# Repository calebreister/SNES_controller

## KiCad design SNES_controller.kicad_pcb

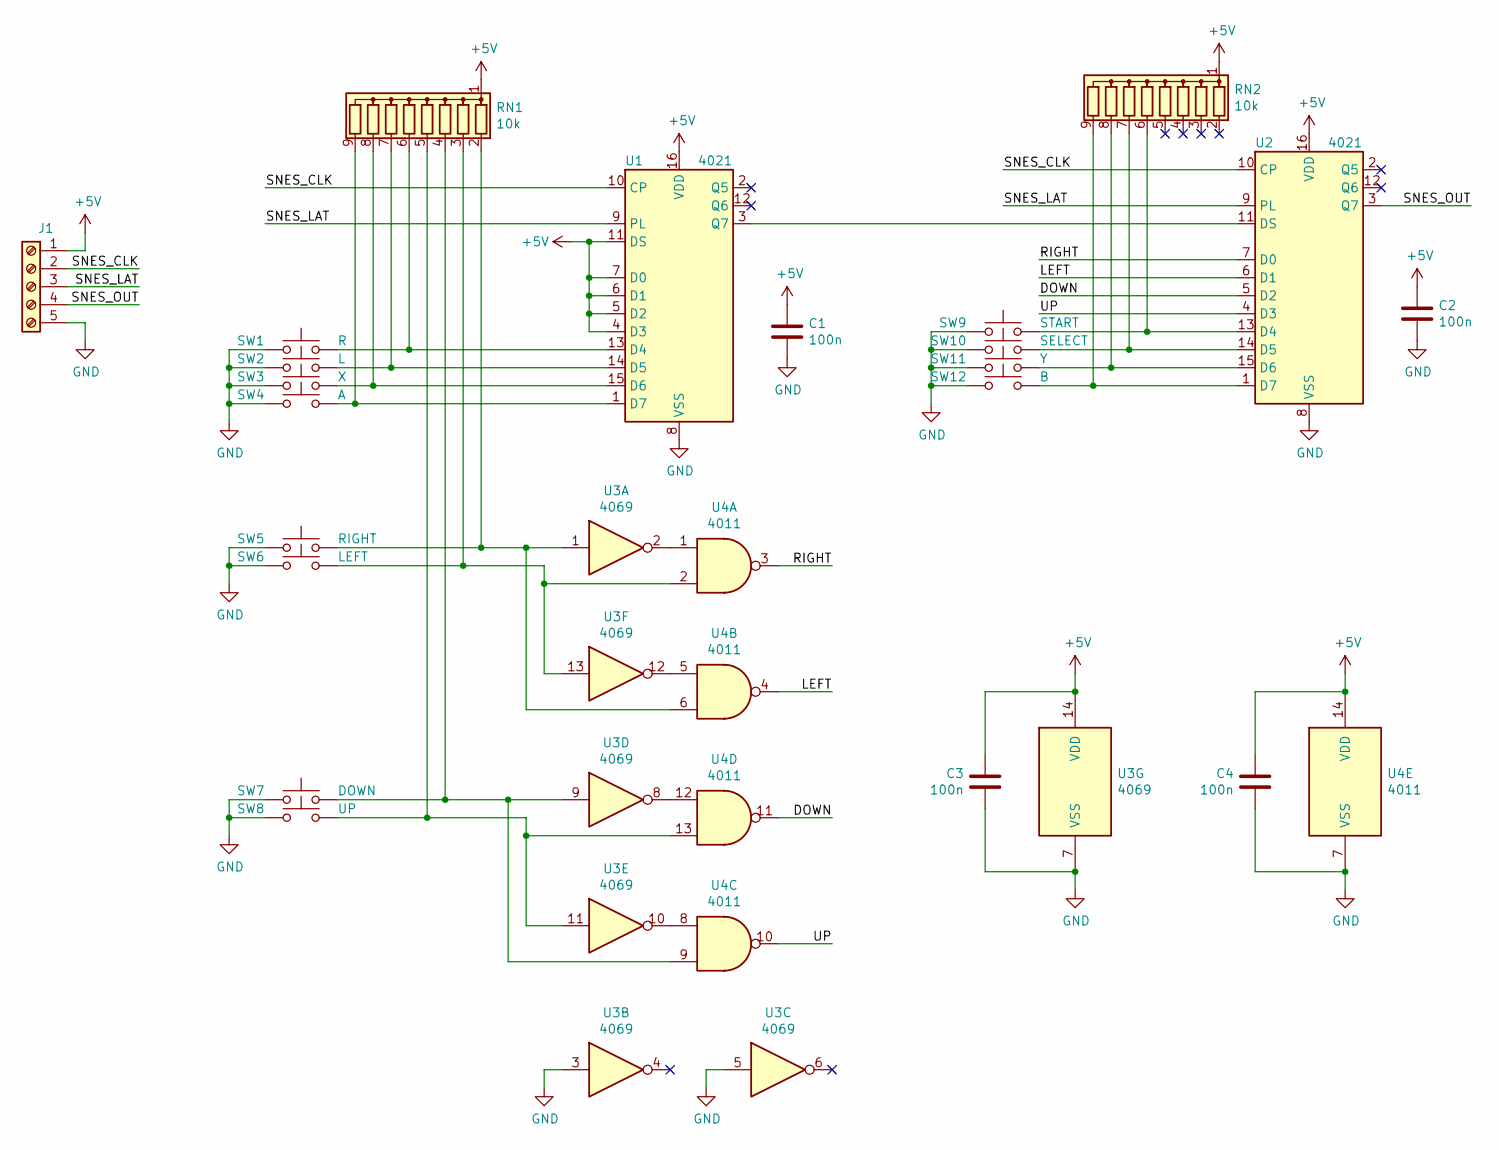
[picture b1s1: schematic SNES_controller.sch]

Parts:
C1, C2, C3, C4: 100n; C_Disc_D5.0mm_W2.5mm_P5.00mm
J1: Conn_01x07; TerminalBlock_Phoenix_MKDS-1,5-5-5.08_1x05_P5.08mm_Horizont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
RN1, RN2: 10k; R_Array_SIP9
SW1: R; JST_XH_B2B-XH-A_1x02_P2.50mm_Vertical
SW2: L; JST_XH_B2B-XH-A_1x02_P2.50mm_Vertical
SW3: X; JST_XH_B2B-XH-A_1x02_P2.50mm_Vertical
SW4: A; JST_XH_B2B-XH-A_1x02_P2.50mm_Vertical
SW5: RIGHT; JST_XH_B2B-XH-A_1x02_P2.50mm_Vertical
SW6: LEFT; JST_XH_B2B-XH-A_1x02_P2.50mm_Vertical
SW7: DOWN; JST_XH_B2B-XH-A_1x02_P2.50mm_Vertical
SW8: UP; JST_XH_B2B-XH-A_1x02_P2.50mm_Vertical
SW9: START; JST_XH_B2B-XH-A_1x02_P2.50mm_Vertical
SW10: SELECT; JST_XH_B2B-XH-A_1x02_P2.50mm_Vertical
SW11: Y; JST_XH_B2B-XH-A_1x02_P2.50mm_Vertical
SW12: B; JST_XH_B2B-XH-A_1x02_P2.50mm_Vertical
U1, U2: 4021; DIP-16_W7.62mm_Socket
U3: 4069; DIP-14_W7.62mm_Socket
U4: 4011; DIP-14_W7.62mm_Socket

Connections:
+5V: C1.1, C2.1, C3.1, C4.1, J1.1, RN1.1 (common), RN2.1 (common), U1.4 (D3), U1.5 (D2), U1.6 (D1), U1.7 (D0), U1.11 (DS), U1.16 (VDD), U2.16 (VDD), U3.14 (VDD), U4.14 (VDD)
/DOWN: U2.5 (D2), U4.11
/LEFT: U2.6 (D1), U4.4
/RIGHT: U2.7 (D0), U4.3
/SNES_CLK: J1.2, U1.10 (CP), U2.10 (CP)
/SNES_LAT: J1.3, U1.9 (PL), U2.9 (PL)
/SNES_OUT: J1.4, U2.3 (Q7)
/UP: U2.4 (D3), U4.10
GND: C1.2, C2.2, C3.2, C4.2, J1.5, SW1.1, SW2.1, SW3.1, SW4.1, SW5.1, SW6.1, SW7.1, SW8.1, SW9.1, SW10.1, SW11.1, SW12.1, U1.8 (VSS), U2.8 (VSS), U3.3, U3.5, U3.7 (VSS), U4.7 (VSS)
unnamed: RN1.2 (R1), SW5.2, U3.1, U4.6
unnamed: RN1.3 (R2), SW6.2, U3.13, U4.2
unnamed: RN1.4 (R3), SW7.2, U3.9, U4.9
unnamed: RN1.5 (R4), SW8.2, U3.11, U4.13
unnamed: RN1.6 (R5), SW1.2, U1.13 (D4)
unnamed: RN1.7 (R6), SW2.2, U1.14 (D5)
unnamed: RN1.8 (R7), SW3.2, U1.15 (D6)
unnamed: RN1.9 (R8), SW4.2, U1.1 (D7)
unnamed: RN2.6 (R5), SW9.2, U2.13 (D4)
unnamed: RN2.7 (R6), SW10.2, U2.14 (D5)
unnamed: RN2.8 (R7), SW11.2, U2.15 (D6)
unnamed: RN2.9 (R8), SW12.2, U2.1 (D7)
unnamed: U1.3 (Q7), U2.11 (DS)
unnamed: U3.2, U4.1
unnamed: U3.8, U4.12
unnamed: U3.10, U4.8
unnamed: U3.12, U4.5

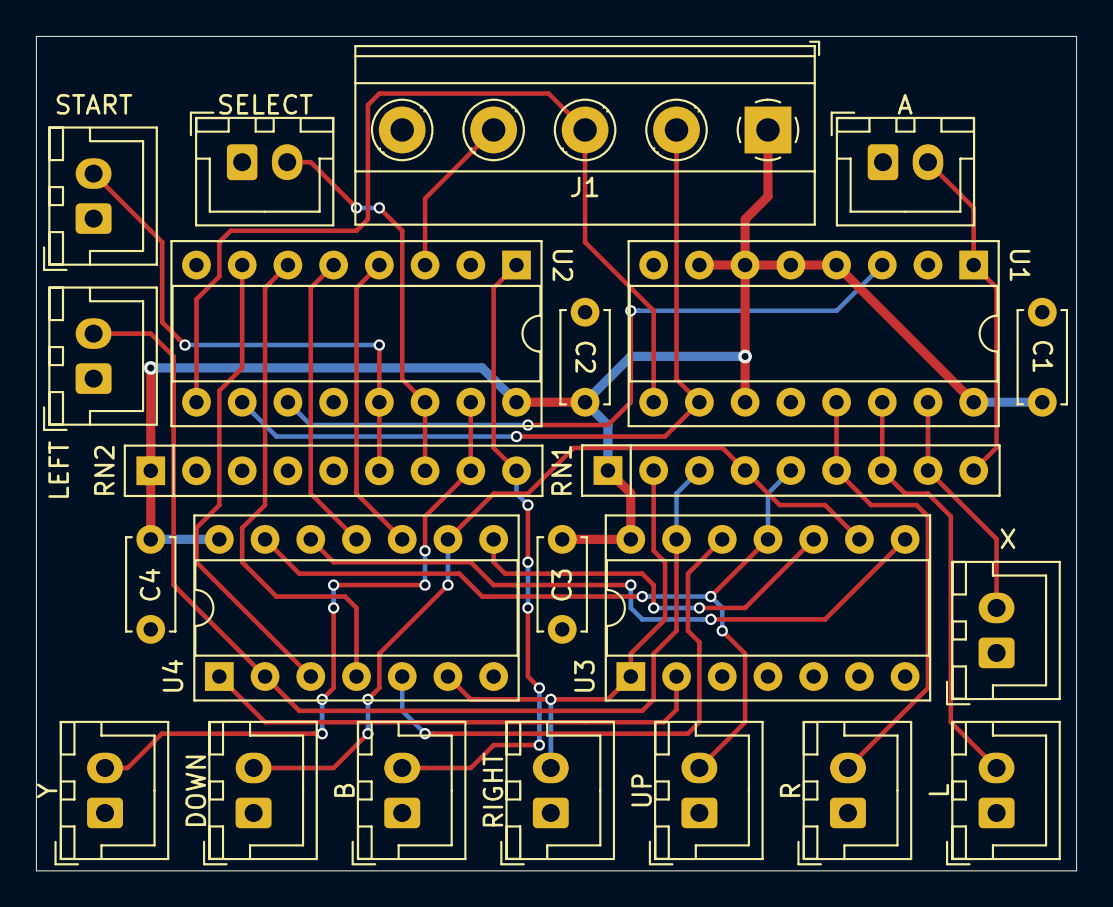
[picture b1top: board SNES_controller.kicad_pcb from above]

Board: 2 copper layers, 57.8 x 46.4 mm, 23 parts (0 on the bottom side), 26 nets.

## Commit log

2020-03-19 Add .gitignore
2020-03-19 Change switches to connectors, add logic to prevent UP/DOWN or LEFT/RIGHT from being pressed simultaneously.
2020-03-19 Reroute PCB with new logic and connectors in place of switches.
2020-03-20 Finish redesign
2020-03-26 Disconnect unnecessary pullups
